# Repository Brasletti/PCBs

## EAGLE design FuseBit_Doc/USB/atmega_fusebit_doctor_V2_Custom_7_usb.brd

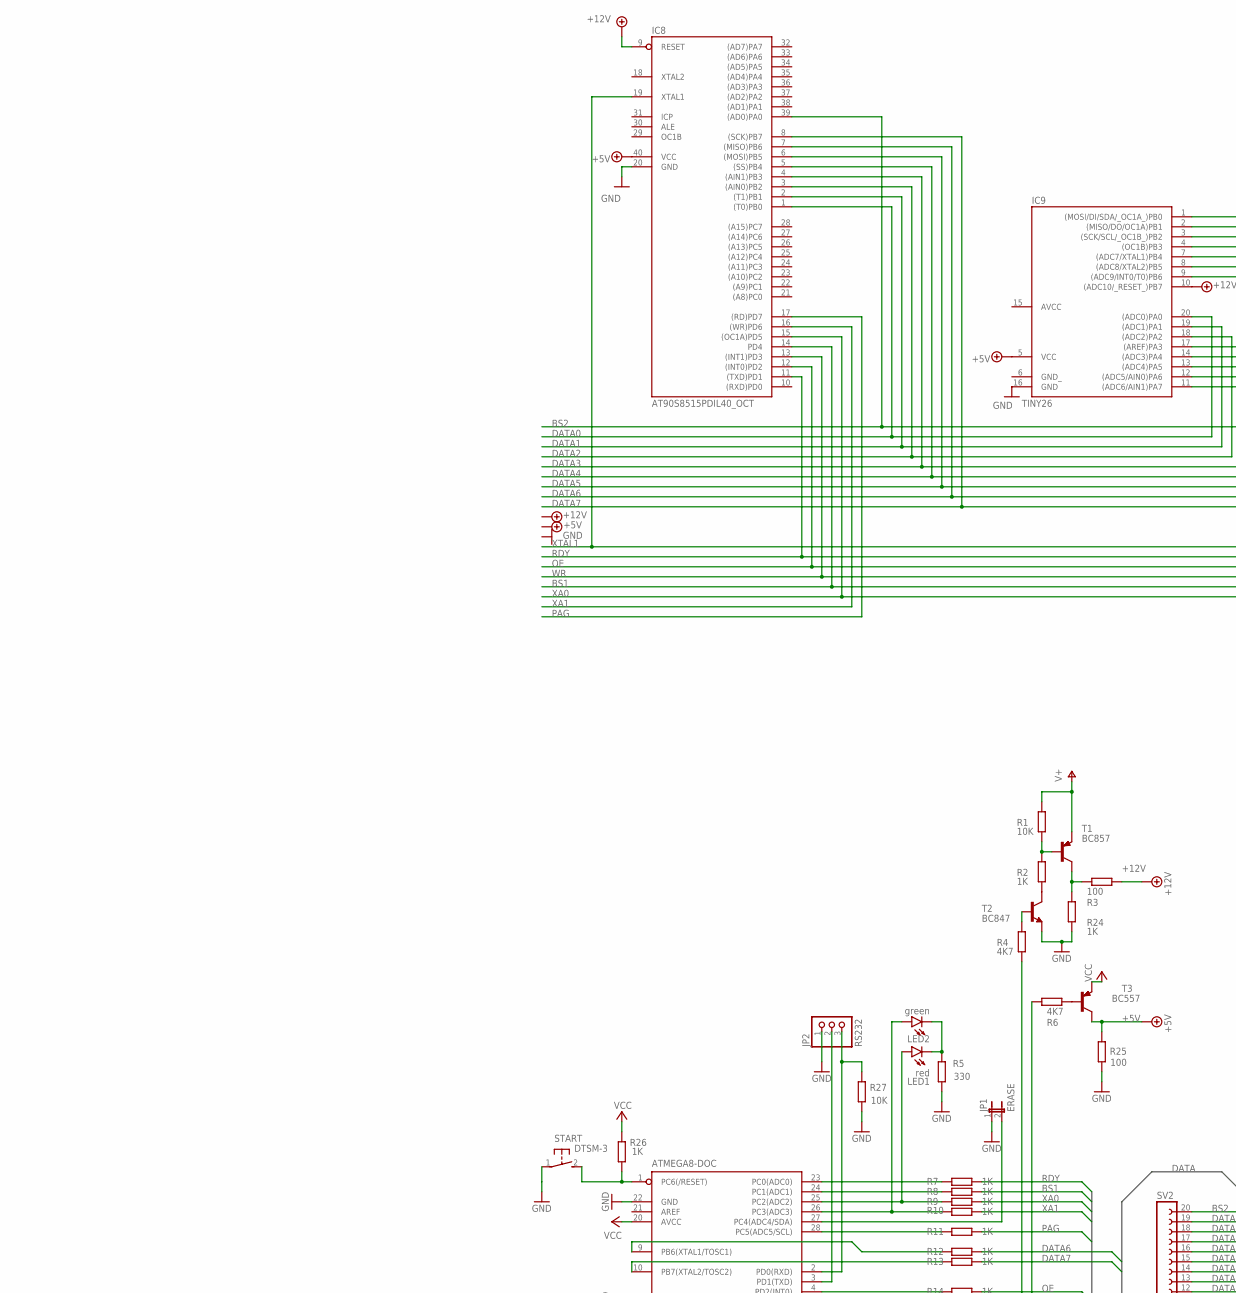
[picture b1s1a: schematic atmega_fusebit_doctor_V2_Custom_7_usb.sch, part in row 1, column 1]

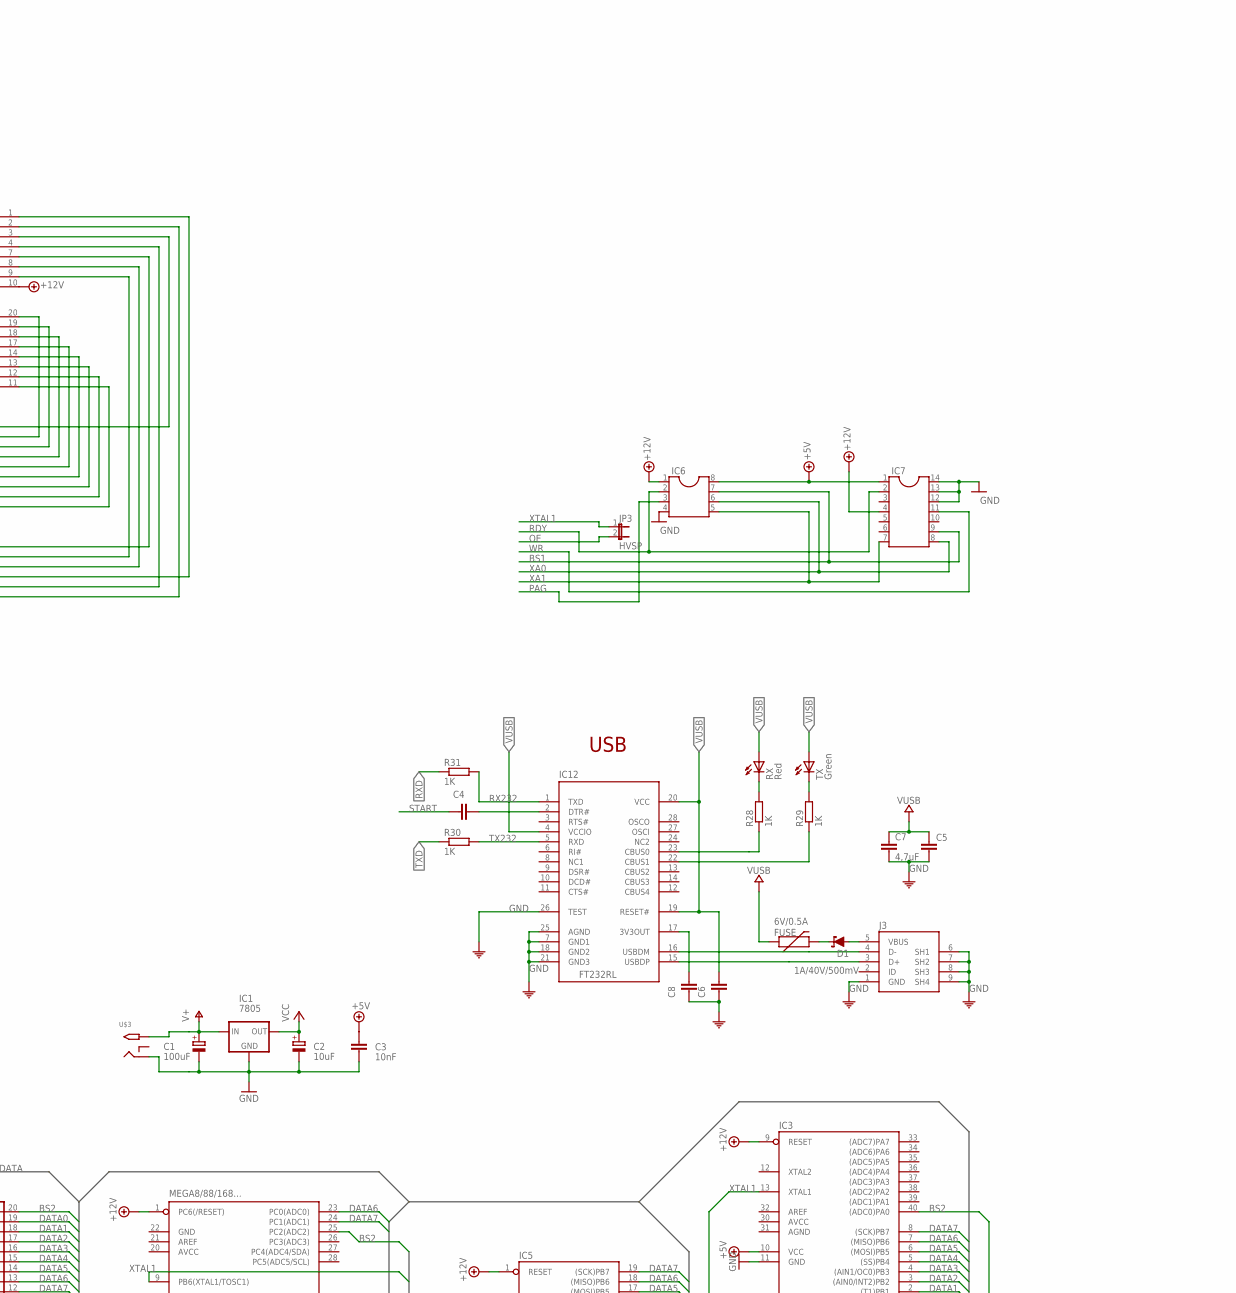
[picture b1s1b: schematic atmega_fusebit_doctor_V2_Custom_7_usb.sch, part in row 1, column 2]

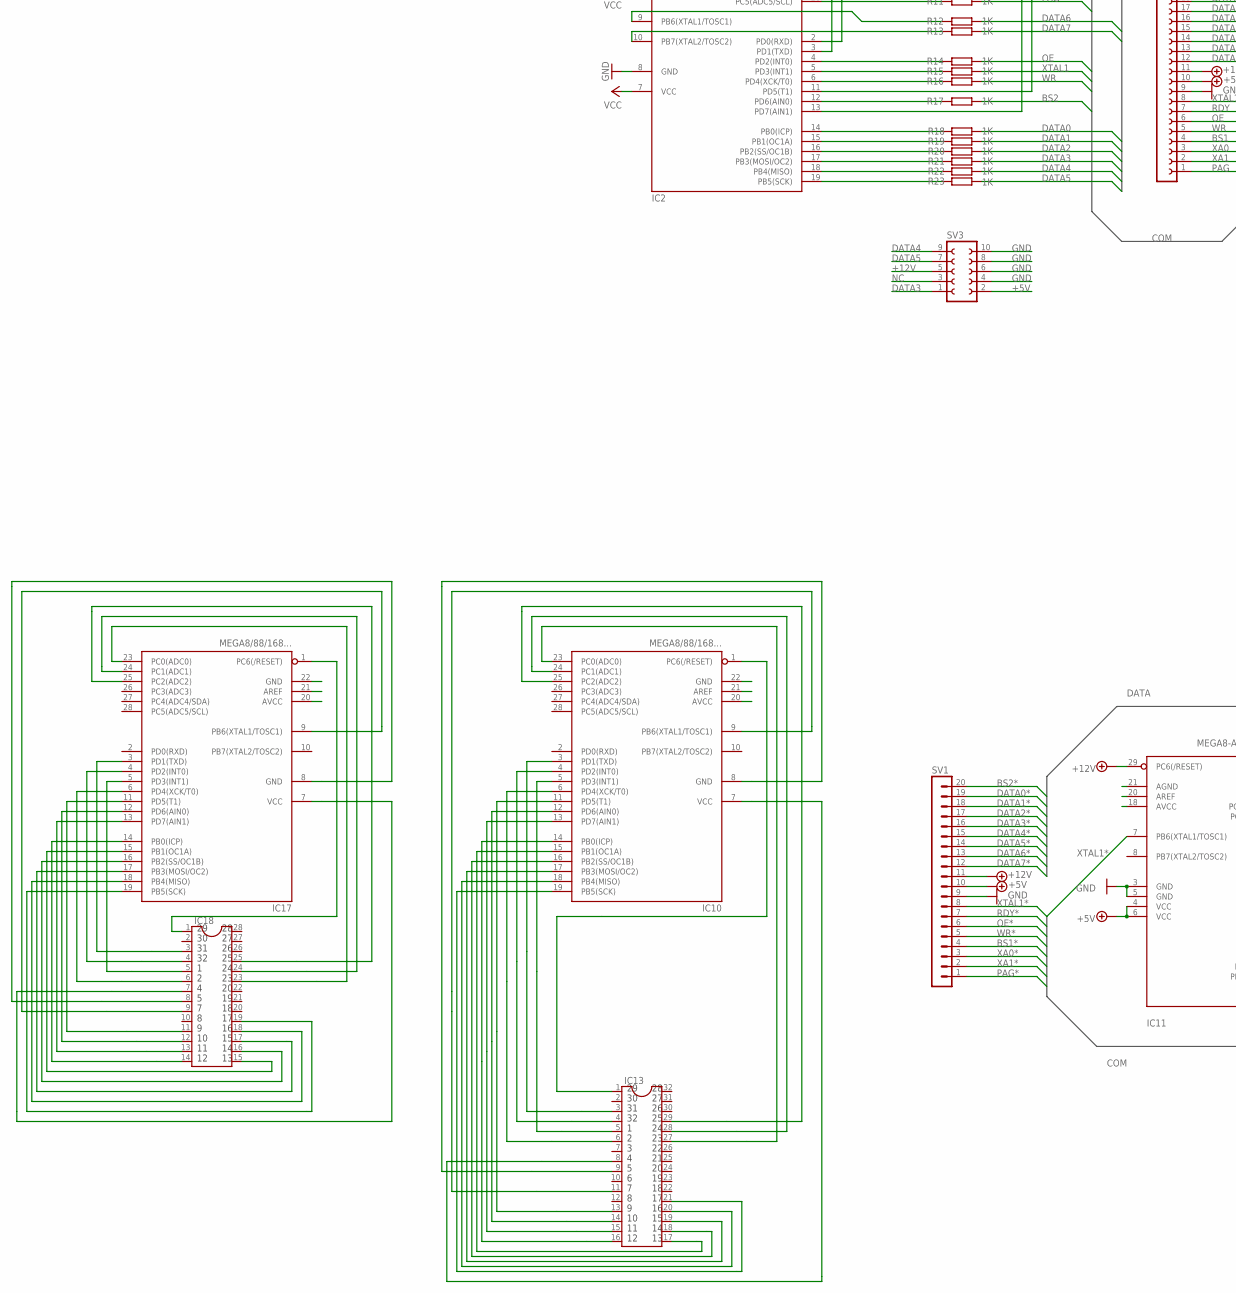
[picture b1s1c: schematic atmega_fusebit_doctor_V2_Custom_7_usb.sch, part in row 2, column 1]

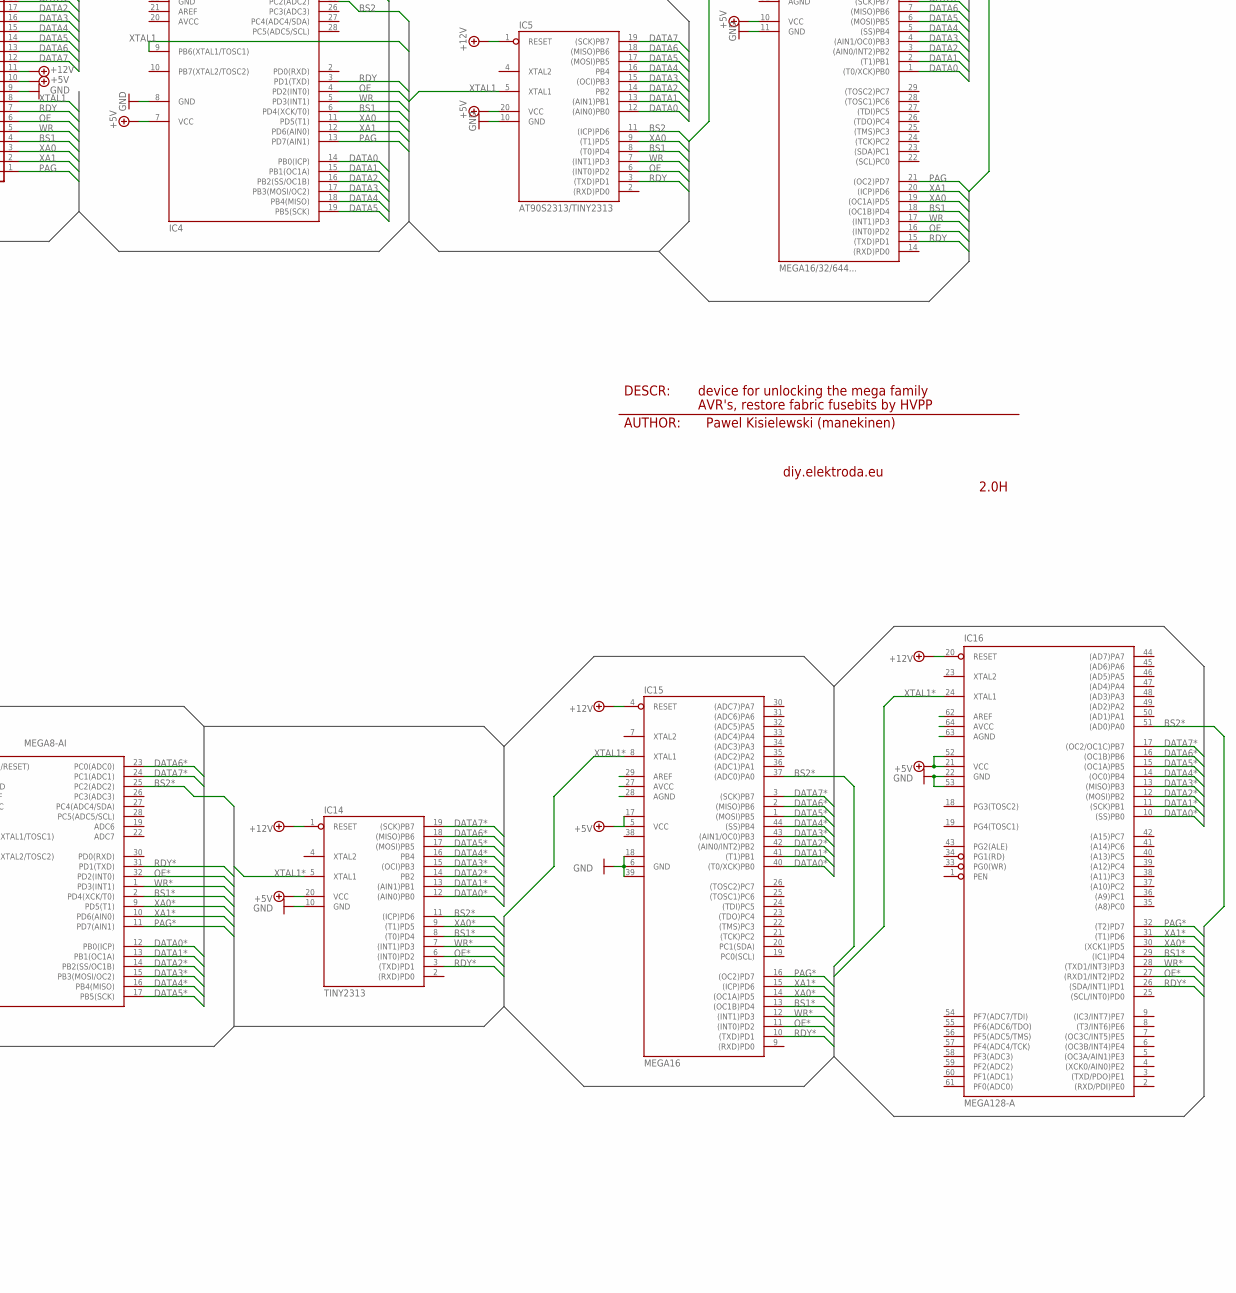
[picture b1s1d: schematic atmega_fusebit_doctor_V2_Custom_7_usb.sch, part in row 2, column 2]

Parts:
C1: 100uF; 153CLV-0605
C2: 10uF; 153CLV-0405
C3: 10nF; C0805
C4, C5, C6, C8: 100nF; C0805
C7: 4,7uF; C1206
D1: 1A/40V/500mV; SMA-DIODE
FUSE: 6V/0.5A; 1206
IC1: 7805; 78XXL
IC2: ATMEGA8-DOC; DIL28-3_OCT
IC3: MEGA16/32/644...; DIL40_OCT
IC4, IC10, IC17: MEGA8/88/168...; DIL28-3_OCT
IC5: AT90S2313/TINY2313; DIL20_OCT
IC6: DIL8S; SOCKED-08
IC7: DIL14S; SOCKED-14
IC8: AT90S8515PDIL40_OCT; DIL40_OCT
IC9: TINY26; DIL20_OCT
IC11: MEGA8-AI; TQFP32-08
IC12: FT232RL; SSOP28
IC13: DIL32
IC14: TINY2313; SO20L
IC15: MEGA16; TQFP44
IC16: MEGA128-A; TQFP64
IC18: DIL28; DIL28-6
J3: 0219_14850; USB-MINI-B_2
JP1: ERASE; JP1
JP2: RS232; 1X03
JP3: HVSP; JP1
LED1: red; LED-1206
LED2: green; LED-1206
R1, R27: 10K; R0805
R2, R7, R8, R9, R10, R11, R12, R13, R14, R15, R16, R17, R18, R19, R20, R21, R22, R23, R24, R26, R28, R29, R30, R31: 1K; R0805
R3, R25: 100; R0805
R4, R6: 4K7; R0805
R5: 330; R0805
RX: Red; CHIPLED_0805
START: DTSM-3
SV1: MA20-1
SV2: FE20-1; FE20
SV3: FE05-2
T1: BC857; SOT23-BEC
T2: BC847; SOT23
T3: BC557; SOT23-BEC
TX: Green; CHIPLED_0805
U$3: 2.1MMJACKTHM; PJ-102A

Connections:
1: IC10.5 (PD3(INT1)), IC13.5
2: IC10.6 (PD4(XCK/T0)), IC13.6
3: IC17.1 (PC6(/RESET)), IC18.1
4: IC10.7 (VCC), IC13.8
5: IC10.8 (GND), IC13.9
7: IC10.9 (PB6(XTAL1/TOSC1)), IC13.11
9: IC10.11 (PD5(T1)), IC13.13
10: IC10.12 (PD6(AIN0)), IC13.14
11: IC10.13 (PD7(AIN1)), IC13.15
12: IC10.14 (PB0(ICP)), IC13.16
13: IC10.15 (PB1(OC1A)), IC13.17
14: IC10.16 (PB2(SS/OC1B)), IC13.18
15: IC10.17 (PB3(MOSI/OC2)), IC13.19
16: IC10.18 (PB4(MISO)), IC13.20
17: IC10.19 (PB5(SCK)), IC13.21
19: IC17.3 (PD1(TXD)), IC18.3
20: IC17.4 (PD2(INT0)), IC18.4
21: IC17.5 (PD3(INT1)), IC18.5
22: IC17.6 (PD4(XCK/T0)), IC18.6
23: IC10.23 (PC0(ADC0)), IC13.27
24: IC10.24 (PC1(ADC1)), IC13.28
25: IC10.25 (PC2(ADC2)), IC13.29
29: IC10.1 (PC6(/RESET)), IC13.1
31: IC10.3 (PD1(TXD)), IC13.3
32: IC10.4 (PD2(INT0)), IC13.4
33: IC17.7 (VCC), IC18.7
34: IC17.8 (GND), IC18.8
35: IC17.9 (PB6(XTAL1/TOSC1)), IC18.9
37: IC17.11 (PD5(T1)), IC18.11
38: IC17.12 (PD6(AIN0)), IC18.12
39: IC17.13 (PD7(AIN1)), IC18.13
40: IC17.14 (PB0(ICP)), IC18.14
41: IC17.15 (PB1(OC1A)), IC18.15
42: IC17.16 (PB2(SS/OC1B)), IC18.16
43: IC17.17 (PB3(MOSI/OC2)), IC18.17
44: IC17.18 (PB4(MISO)), IC18.18
45: IC17.19 (PB5(SCK)), IC18.19
47: IC17.23 (PC0(ADC0)), IC18.23
48: IC17.24 (PC1(ADC1)), IC18.24
49: IC17.25 (PC2(ADC2)), IC18.25
+5V: C3.1, IC3.10 (VCC), IC4.7 (VCC), IC5.20 (VCC), IC6.8, IC7.1, IC8.40 (VCC), IC9.5 (VCC), R25.2, SV2.10, SV3.2, T3.C
+5V*: IC11.4 (VCC), IC11.6 (VCC), IC14.20 (VCC), IC15.5 (VCC), IC15.17 (VCC1), IC16.21 (VCC), IC16.52 (VCC1), SV1.10
+12V: IC3.9 (RESET), IC4.1 (PC6(/RESET)), IC5.1 (RESET), IC6.1, IC7.4, IC8.9 (RESET), IC9.10 ((ADC10/_RESET_)PB7), R3.2, SV2.11, SV3.5
+12V*: IC11.29 (PC6(/RESET)), IC14.1 (RESET), IC15.4 (RESET), IC16.20 (RESET), SV1.11
AGND: IC3.31 (AGND)
AREF: IC3.32 (AREF)
AVCC: IC3.30 (AVCC), IC4.20 (AVCC), IC9.15 (AVCC)
BS1: IC3.18 ((OC1B)PD4), IC4.6 (PD4(XCK/T0)), IC5.8 ((T0)PD4), IC6.7, IC7.9, IC8.14 (PD4), IC9.4 ((OC1B)PB3), R8.2, SV2.4
BS1*: IC11.2 (PD4(XCK/T0)), IC14.8 ((T0)PD4), IC15.13 ((OC1B)PD4), IC16.29 ((IC1)PD4), SV1.4
BS2: IC3.40 ((ADC0)PA0), IC4.25 (PC2(ADC2)), IC5.11 ((ICP)PD6), IC8.39 ((AD0)PA0), IC9.3 ((SCK/SCL/_OC1B_)PB2), R17.2, SV2.20
BS2*: IC11.25 (PC2(ADC2)), IC14.11 ((ICP)PD6), IC15.37 ((ADC0)PA0), IC16.51 ((AD0)PA0), SV1.20
COM: C6.1, C8.1
DATA0: IC3.1 ((T0/XCK)PB0), IC4.14 (PB0(ICP)), IC5.12 ((AIN0)PB0), IC8.1 ((T0)PB0), IC9.20 ((ADC0)PA0), R18.2, SV2.19
DATA0*: IC11.12 (PB0(ICP)), IC14.12 ((AIN0)PB0), IC15.40 ((T0/XCK)PB0), IC16.10 ((SS)PB0), SV1.19
DATA1: IC3.2 ((T1)PB1), IC4.15 (PB1(OC1A)), IC5.13 ((AIN1)PB1), IC8.2 ((T1)PB1), IC9.19 ((ADC1)PA1), R19.2, SV2.18
DATA1*: IC11.13 (PB1(OC1A)), IC14.13 ((AIN1)PB1), IC15.41 ((T1)PB1), IC16.11 ((SCK)PB1), SV1.18
DATA2: IC3.3 ((AIN0/INT2)PB2), IC4.16 (PB2(SS/OC1B)), IC5.14 (PB2), IC8.3 ((AIN0)PB2), IC9.18 ((ADC2)PA2), R20.2, SV2.17
DATA2*: IC11.14 (PB2(SS/OC1B)), IC14.14 (PB2), IC15.42 ((AIN0/INT2)PB2), IC16.12 ((MOSI)PB2), SV1.17
DATA3: IC3.4 ((AIN1/OC0)PB3), IC4.17 (PB3(MOSI/OC2)), IC5.15 ((OCI)PB3), IC8.4 ((AIN1)PB3), IC9.17 ((AREF)PA3), R21.2, SV2.16, SV3.1
DATA3*: IC11.15 (PB3(MOSI/OC2)), IC14.15 ((OCI)PB3), IC15.43 ((AIN1/OC0)PB3), IC16.13 ((MISO)PB3), SV1.16
DATA4: IC3.5 ((SS)PB4), IC4.18 (PB4(MISO)), IC5.16 (PB4), IC8.5 ((SS)PB4), IC9.14 ((ADC3)PA4), R22.2, SV2.15, SV3.9
DATA4*: IC11.16 (PB4(MISO)), IC14.16 (PB4), IC15.44 ((SS)PB4), IC16.14 ((OC0)PB4), SV1.15
DATA5: IC3.6 ((MOSI)PB5), IC4.19 (PB5(SCK)), IC5.17 ((MOSI)PB5), IC8.6 ((MOSI)PB5), IC9.13 ((ADC4)PA5), R23.2, SV2.14, SV3.7
DATA5*: IC11.17 (PB5(SCK)), IC14.17 ((MOSI)PB5), IC15.1 ((MOSI)PB5), IC16.15 ((OC1A)PB5), SV1.14
DATA6: IC3.7 ((MISO)PB6), IC4.23 (PC0(ADC0)), IC5.18 ((MISO)PB6), IC8.7 ((MISO)PB6), IC9.12 ((ADC5/AIN0)PA6), R12.2, SV2.13
DATA6*: IC11.23 (PC0(ADC0)), IC14.18 ((MISO)PB6), IC15.2 ((MISO)PB6), IC16.16 ((OC1B)PB6), SV1.13
DATA7: IC3.8 ((SCK)PB7), IC4.24 (PC1(ADC1)), IC5.19 ((SCK)PB7), IC8.8 ((SCK)PB7), IC9.11 ((ADC6/AIN1)PA7), R13.2, SV2.12
DATA7*: IC11.24 (PC1(ADC1)), IC14.19 ((SCK)PB7), IC15.3 ((SCK)PB7), IC16.17 ((OC2/OC1C)PB7), SV1.12
GND: C1.-, C2.-, C3.2, C5.2, C7.2, IC1.GND, IC2.8 (GND), IC2.22 (GND), IC3.11 (GND), IC4.8 (GND), IC4.22 (GND), IC5.10 (GND), IC6.4, IC7.12, IC7.13, IC7.14, IC8.20 (GND), IC9.16 (GND), IC12.7 (GND1), IC12.18 (GND2), IC12.21 (GND3), IC12.25 (AGND), IC12.26 (TEST), J3.1 (GND), J3.6 (SH1), J3.7 (SH2), J3.8 (SH3), J3.9 (SH4), JP1.1, JP2.1, R5.1, R24.1, R25.1, R27.2, START.1, SV2.9, SV3.4, SV3.6, SV3.8, SV3.10, T2.2 (E), U$3.RING
GND*: IC11.3 (GND), IC11.5 (GND), IC14.10 (GND), IC15.6 (GND), IC15.18 (GND1), IC15.39 (GND2), IC16.22 (GND), IC16.53 (GND1), SV1.9
GND_: IC9.6 (GND_)
unnamed: R6.1, T3.B
unnamed: IC2.14 (PB0(ICP)), R18.1
unnamed: C8.2, IC12.17 (3V3OUT)
unnamed: IC2.28 (PC5(ADC5/SCL)), R11.1
unnamed: IC2.6 (PD4(XCK/T0)), R16.1
unnamed: IC2.4 (PD2(INT0)), R14.1
unnamed: R2.2, T2.3 (C)
unnamed: IC2.9 (PB6(XTAL1/TOSC1)), R12.1
unnamed: IC2.10 (PB7(XTAL2/TOSC2)), R13.1
unnamed: IC2.13 (PD7(AIN1)), R4.2
unnamed: IC2.11 (PD5(T1)), R6.2
unnamed: IC2.15 (PB1(OC1A)), R19.1
unnamed: IC2.16 (PB2(SS/OC1B)), R20.1
unnamed: IC2.5 (PD3(INT1)), R15.1
unnamed: IC2.23 (PC0(ADC0)), R7.1
unnamed: R3.1, R24.2, T1.C
unnamed: IC2.17 (PB3(MOSI/OC2)), R21.1
unnamed: IC2.18 (PB4(MISO)), R22.1
unnamed: IC2.19 (PB5(SCK)), R23.1
unnamed: IC2.12 (PD6(AIN0)), R17.1
unnamed: R4.1, T2.1 (B)
unnamed: IC2.27 (PC4(ADC4/SDA)), JP1.2
unnamed: LED1.C, LED2.C, R5.2
unnamed: R1.2, R2.1, T1.B
unnamed: C4.2, IC12.2 (DTR#)
unnamed: IC2.24 (PC1(ADC1)), R8.1
unnamed: IC12.15 (USBDP), J3.3 (D+)
unnamed: IC12.16 (USBDM), J3.4 (D-)
unnamed: IC12.23 (CBUS0), R28.1
unnamed: IC2.26 (PC3(ADC3)), LED2.A, R10.1
unnamed: IC2.25 (PC2(ADC2)), LED1.A, R9.1
unnamed: IC12.22 (CBUS1), R29.1
unnamed: R28.2, RX.C
unnamed: R29.2, TX.C
NC: SV3.3
OE: IC3.16 ((INT0)PD2), IC4.4 (PD2(INT0)), IC5.6 ((INT0)PD2), IC8.12 ((INT0)PD2), IC9.8 ((ADC8/XTAL2)PB5), JP3.2, R14.2, SV2.6
OE*: IC11.32 (PD2(INT0)), IC14.6 ((INT0)PD2), IC15.11 ((INT0)PD2), IC16.27 ((RXD1/INT2)PD2), SV1.6
PAG: IC3.21 ((OC2)PD7), IC4.13 (PD7(AIN1)), IC6.3, IC8.17 ((RD)PD7), R11.2, SV2.1
PAG*: IC11.11 (PD7(AIN1)), IC15.16 ((OC2)PD7), IC16.32 ((T2)PD7), SV1.1
RDY: IC3.15 ((TXD)PD1), IC4.3 (PD1(TXD)), IC5.3 ((TXD)PD1), IC6.2, IC7.2, IC8.11 ((TXD)PD1), IC9.9 ((ADC9/INT0/T0)PB6), R7.2, SV2.7
RDY*: IC11.31 (PD1(TXD)), IC14.3 ((TXD)PD1), IC15.10 ((TXD)PD1), IC16.26 ((SDA/INT1)PD1), SV1.7
RX232: IC12.1 (TXD), R31.2
RXD: IC2.2 (PD0(RXD)), JP2.3, R27.1, R31.1
START: C4.1, IC2.1 (PC6(/RESET)), R26.1, START.2
TX232: IC12.5 (RXD), R30.2
TXD: IC2.3 (PD1(TXD)), JP2.2, R30.1
V+: C1.+, IC1.IN, R1.1, T1.E, U$3.TIP
VCC: C2.+, IC1.OUT, IC2.7 (VCC), IC2.20 (AVCC), R26.2, T3.E
VCC2: IC15.38 (VCC2)
VUSB: C5.1, C6.2, C7.1, FUSE.1, IC12.4 (VCCIO), IC12.19 (RESET#), IC12.20 (VCC), RX.A, TX.A
VUSB_PREFUSE: D1.C, FUSE.2
VUSB_RAW: D1.A, J3.5 (VBUS)
WR: IC3.17 ((INT1)PD3), IC4.5 (PD3(INT1)), IC5.7 ((INT1)PD3), IC7.11, IC8.13 ((INT1)PD3), IC9.1 ((MOSI/DI/SDA/_OC1A_)PB0), R16.2, SV2.5
WR*: IC11.1 (PD3(INT1)), IC14.7 ((INT1)PD3), IC15.12 ((INT1)PD3), IC16.28 ((TXD1/INT3)PD3), SV1.5
XA0: IC3.19 ((OC1A)PD5), IC4.11 (PD5(T1)), IC5.9 ((T1)PD5), IC6.6, IC7.8, IC8.15 ((OC1A)PD5), IC9.2 ((MISO/DO/OC1A)PB1), R9.2, SV2.3
XA0*: IC11.9 (PD5(T1)), IC14.9 ((T1)PD5), IC15.14 ((OC1A)PD5), IC16.30 ((XCK1)PD5), SV1.3
XA1: IC3.20 ((ICP)PD6), IC4.12 (PD6(AIN0)), IC6.5, IC7.7, IC8.16 ((WR)PD6), R10.2, SV2.2
XA1*: IC11.10 (PD6(AIN0)), IC15.15 ((ICP)PD6), IC16.31 ((T1)PD6), SV1.2
XTAL1: IC3.13 (XTAL1), IC4.9 (PB6(XTAL1/TOSC1)), IC5.5 (XTAL1), IC8.19 (XTAL1), IC9.7 ((ADC7/XTAL1)PB4), JP3.1, R15.2, SV2.8
XTAL1*: IC11.7 (PB6(XTAL1/TOSC1)), IC14.5 (XTAL1), IC15.8 (XTAL1), IC16.24 (XTAL1), SV1.8

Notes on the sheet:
AUTHOR:
DESCR:
device for unlocking the mega family
AVR's, restore fabric fusebits by HVPP
Pawel Kisielewski (manekinen)
2.0H
diy.elektroda.eu
USB

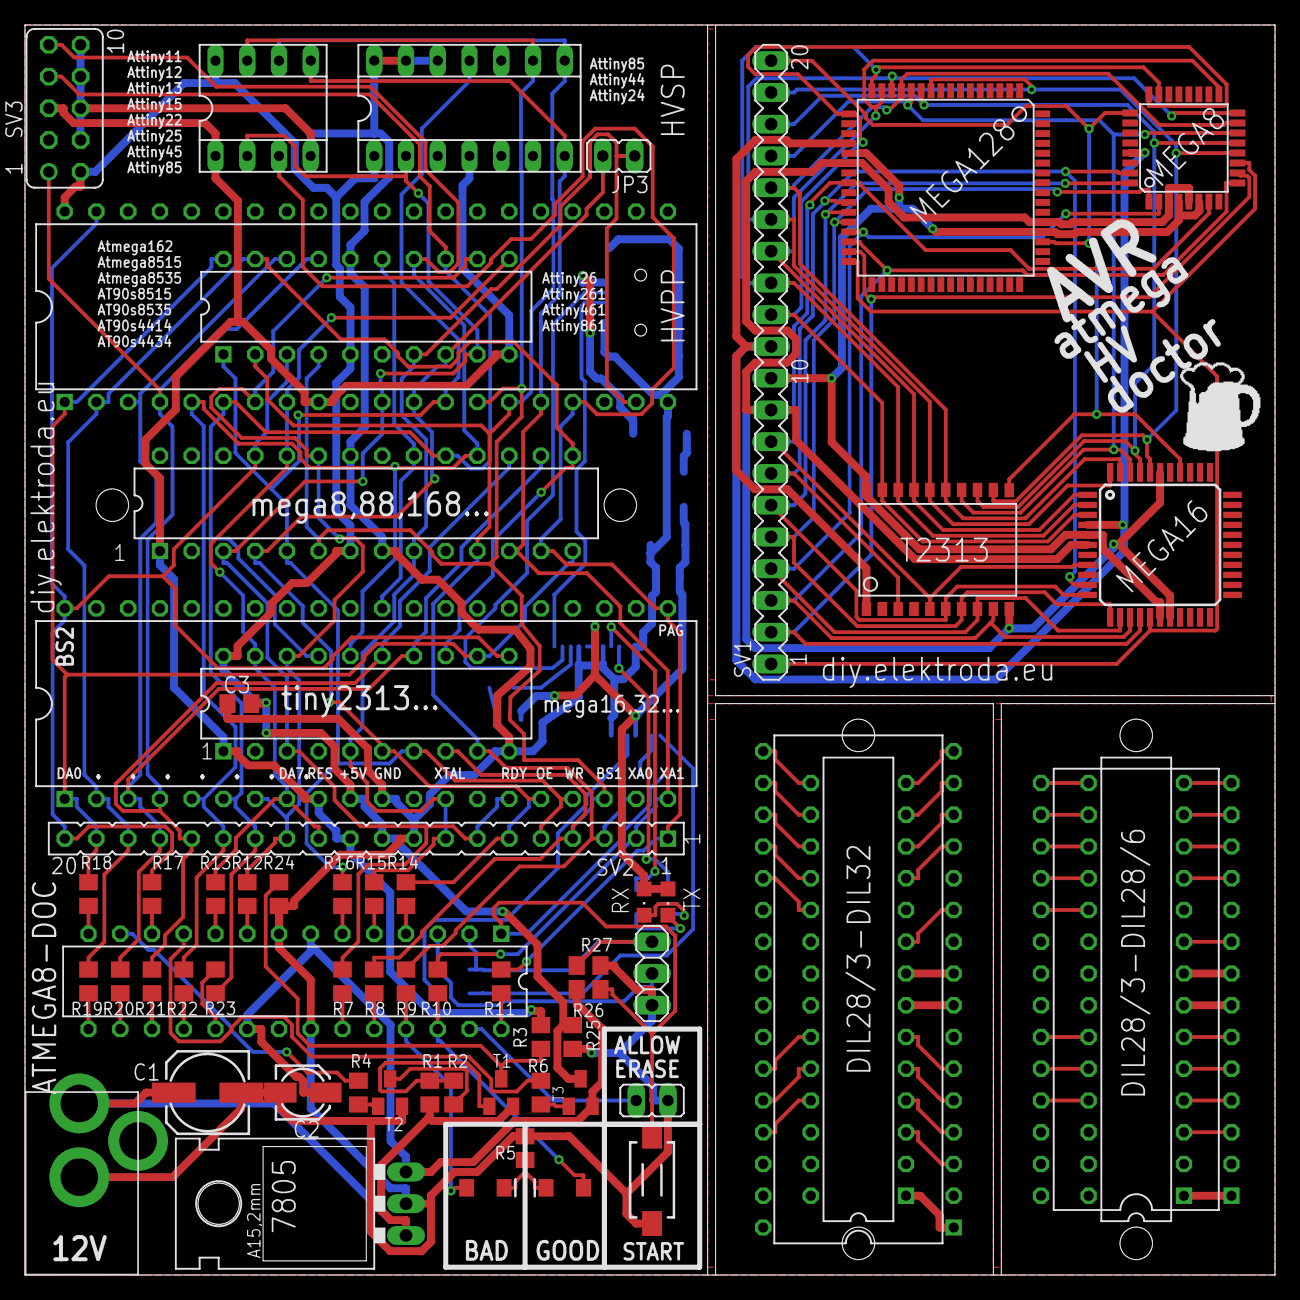
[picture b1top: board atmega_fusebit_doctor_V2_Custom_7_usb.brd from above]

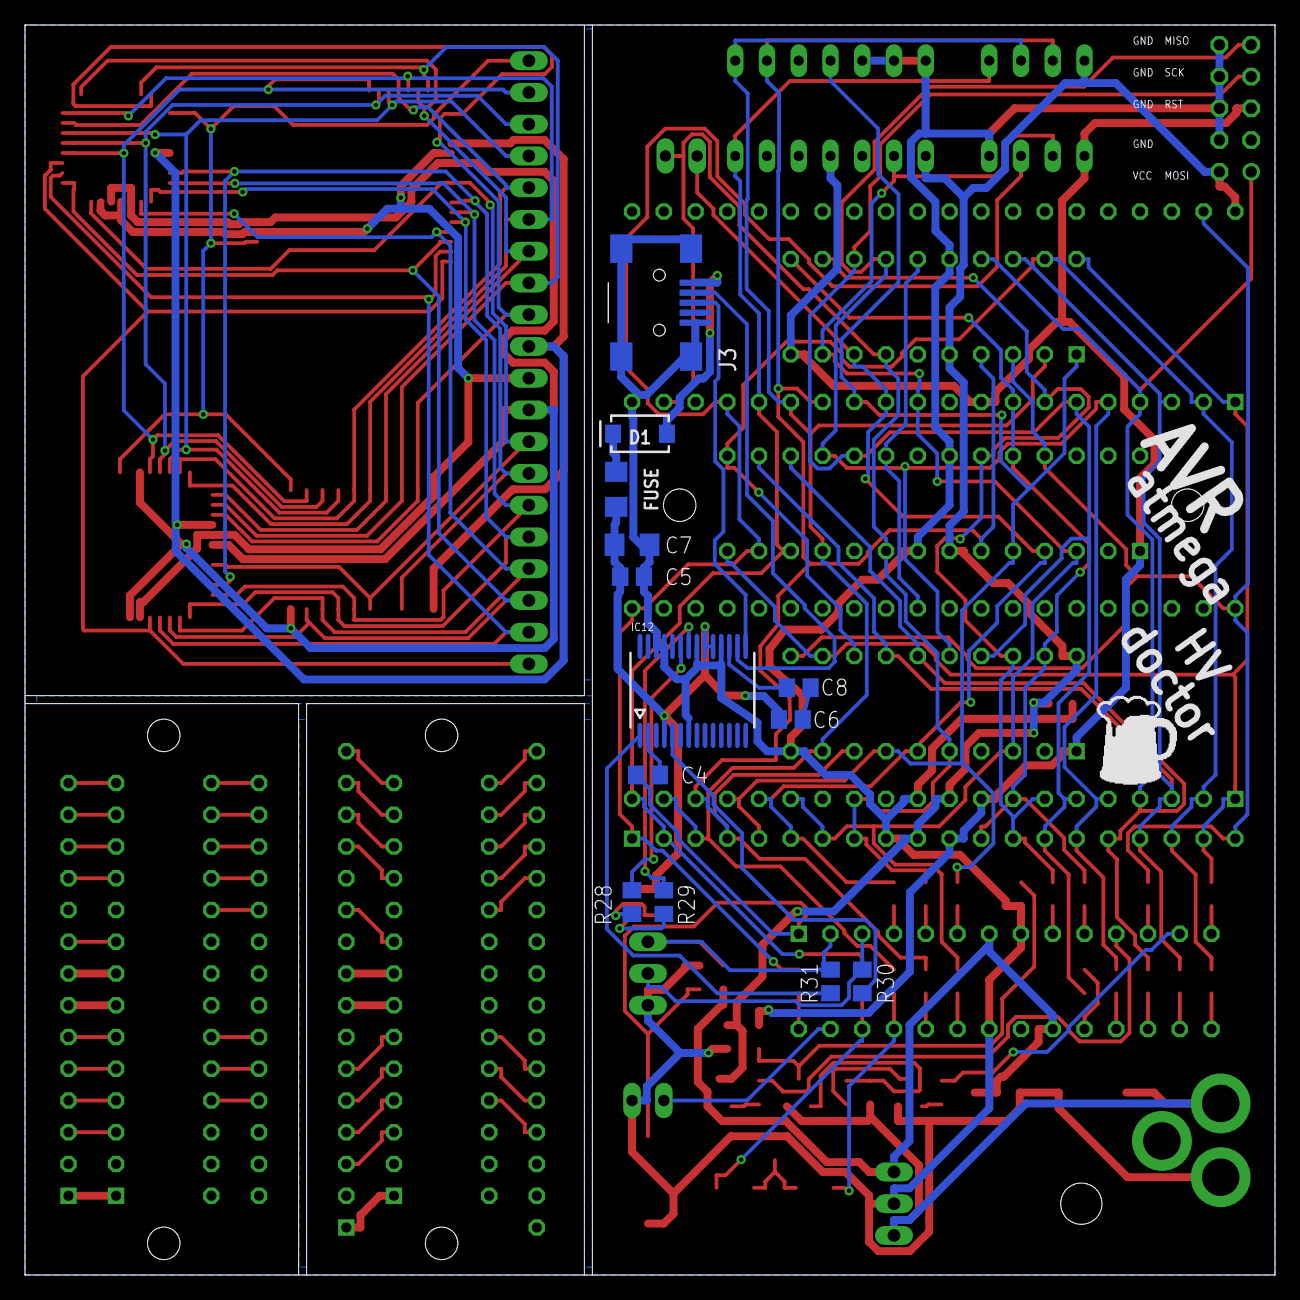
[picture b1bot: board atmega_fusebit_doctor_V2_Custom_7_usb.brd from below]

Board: 2 copper layers, 100.0 x 100.0 mm, 75 parts (13 on the bottom side), 126 nets.

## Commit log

2018-04-07 Fusebit_Doc_Custom_V1
2018-04-08 FT232_update
2021-06-02 Added Gerber Files

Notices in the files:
parts and their libraries:
SparkFun-LED: Licensing: Creative Commons ShareAlike 4.0 International - https://creativecommons.org/licenses/by-sa/4.0
